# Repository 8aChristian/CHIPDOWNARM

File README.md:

# CHIPDOWNARM | Sub-GHz LoRaWAN & Industrial Telemetry Node

CHIPDOWNARM is a highly optimized, industrial-grade IoT telemetry edge node designed for mission-critical Sub-GHz LPWAN networks, remote monitoring, and smart agriculture deployments. Built around the high-performance **STMicroelectronics STM32WLE5** (ARM Cortex-M4 with integrated Sub-GHz LoRa/FSK transceiver), it delivers robust long-range communication with an ultra-low power footprint.

The board follows rigorous IPC (IPC-2152, IPC-2221) standards, featuring a wide-input high-efficiency switching power architecture (TPS62840), a highly stable 32MHz TCXO for RF precision, and an optimized 4-layer controlled-impedance stackup for impeccable RF Signal Integrity (SI) and Power Integrity (PI).

---

## 📸 Photorealistic 3D Renders

---

## 🏛️ System Architecture Diagram

```mermaid
flowchart TD
    subgraph PowerDomain["⚡ Power Architecture (1.8V - 6.5V)"]
        VIN["DC Power In (J1) / Li-SOCl2 / Li-Po"] --> F1["Polyfuse PTC (F1)"]
        F1 --> D1["TVS Diode Protection"]
        D1 --> U2["TI TPS62840 Buck (60nA Iq)"]
        U2 --> L1["1.5µH Shielded Inductor"]
        L1 --> VCC3["+3V0 System Rail"]
        VCC3 --> FB1["Ferrite Bead (FB1)"]
        FB1 --> VDDA["Filtered Analog Power (VDDA)"]
    end

    subgraph CoreDomain["🧠 Compute and RF Engine"]
        U1["STM32WLE5CCU6 (ARM Cortex-M4 @ 48MHz)"]
        Y1["32.000 MHz TCXO (Y1)"] -->|"RF Master Clock"| U1
        Y2["32.768 kHz RTC Crystal (Y2)"] -->|"Low Power RTC"| U1
        VCC3 --> U1
        VDDA --> U1
    end

    subgraph RFDomain["📡 Sub-GHz RF Frontend (150-960 MHz)"]
        U1 -->|"RF_PA_OUT"| RFFilt["LC Harmonics Filter & Matching Network"]
        RFFilt -->|"50Ω Coplanar Microstrip"| J2["SMA Edge-Mount Connector (J2)"]
    end

    subgraph SensorDomain["🌡️ Telemetry and Sensing"]
        U3["Sensirion SHTC3 (I2C)"] -->|"I2C1_SCL / I2C1_SDA"| U1
        VCC3 --> U3
    end

    subgraph DebugDomain["🔧 Diagnostics and Programming"]
        J3["Tag-Connect TC2030-IDC-NL"] -->|"SWDIO, SWCLK, NRST, SWO"| U1
    end

    classDef pwr fill:#f97316,stroke:#c2410c,stroke-width:2px,color:#fff;
    classDef core fill:#2563eb,stroke:#1d4ed8,stroke-width:2px,color:#fff;
    classDef rf fill:#16a34a,stroke:#15803d,stroke-width:2px,color:#fff;
    classDef sns fill:#9333ea,stroke:#7e22ce,stroke-width:2px,color:#fff;
    classDef dbg fill:#475569,stroke:#334155,stroke-width:2px,color:#fff;

    class PowerDomain,VIN,F1,D1,U2,L1,VCC3,FB1,VDDA pwr;
    class CoreDomain,U1,Y1,Y2 core;
    class RFDomain,RFFilt,J2 rf;
    class SensorDomain,U3 sns;
    class DebugDomain,J3 dbg;
```

---

## ⚡ Power Tree & Energy Profile

```mermaid
flowchart LR
    BATT["Battery / External Input<br/><b>1.8V - 6.5V</b>"] -->|F1: PTC Fuse| REG["TPS62840<br/><b>Buck Regulator</b><br/>Iq = 60 nA | Eff = 92%"]
    REG -->|VOUT = 3.0V| RAIL["+3V0 System Rail<br/>(Inner Layer 2 Plane)"]
    
    RAIL -->|"100nF + 4.7µF"| MCU["STM32WLE5 Core<br/>Sleep: 1.1 µA<br/>TX (+22dBm): 118 mA"]
    RAIL -->|"100nF"| SENS["SHTC3 Sensor<br/>Active: 800 µA<br/>Sleep: 0.2 µA"]
    RAIL -->|"100nF + TCXO Reg"| TCXO["32 MHz TCXO<br/>Warmup: 2 ms"]
    RAIL -->|FB1: Ferrite Filter| RF_ANA["RF & VDDA Power<br/>Multi-stage decoupling"]
```

---

## 🔬 PCB Layer Stackup & Controlled Impedance

The PCB is built on an industrial 4-Layer standard stackup (1.6mm nominal thickness, 1 oz / 35µm copper outer and inner layers) to guarantee excellent RF containment.

```text
========================================================================================
Layer 1 (Top / F.Cu): Component SMD Pads, 50Ω RF Coplanar Microstrips, Buck Power Loop
---------------------------------- Dielectric Prepreg (0.21mm, FR-4, Er=4.5) -----------
Layer 2 (Inner 1 / In1.Cu): Solid Continuous Ground Plane (GND) - Zero Slots
---------------------------------- Core Dielectric (1.065mm, FR-4, Er=4.5) -------------
Layer 3 (Inner 2 / In2.Cu): Dedicated +3V0 Power Plane & RF Return Shield
---------------------------------- Dielectric Prepreg (0.21mm, FR-4, Er=4.5) -----------
Layer 4 (Bottom / B.Cu): Digital Control Signals & Secondary Ground Shield
========================================================================================
```

### 🗺️ Individual Layer Vector Views

| Layer | Type | Function & High-Speed Details | Vector Preview |
| :--- | :--- | :--- | :--- |
| **L1 (F.Cu)** | Signal / RF | 50Ω Coplanar RF track, SMPS power loop, MCU breakouts | [View SVG](docs/img/layer_l1_top.svg) |
| **L2 (In1.Cu)** | Solid GND | 100% continuous reference ground, zero ground slots | [View SVG](docs/img/layer_l2_gnd.svg) |
| **L3 (In2.Cu)** | Power | Dedicated +3V0 power plane, ultra-low impedance distribution | [View SVG](docs/img/layer_l3_pwr.svg) |
| **L4 (B.Cu)** | Signal / Shield | I2C routing, debug traces, stitched ground plane | [View SVG](docs/img/layer_l4_bottom.svg) |

---

## ⚡ Technical Specifications

| Parameter | Specification | Engineering Details |
| :--- | :--- | :--- |
| **Input Supply Voltage** | **1.8V − 6.5V DC** | Polyfuse protection (F1) + Battery input conditioning for Li-Po/Li-SOCl2. |
| **Main Step-Down Converter** | **TI TPS62840 (1.8V-6.5V)** | Ultra-low $I_q$ (60 nA) high-efficiency buck regulator with compact shielded inductor. |
| **Main Processing Unit (MCU)** | **STM32WLE5CCU6** | ARM Cortex-M4 @ 48MHz, 256KB Flash, 64KB SRAM, integrated Sub-GHz Radio. |
| **Wireless Connectivity** | **LoRa / (G)FSK / (G)MSK** | Sub-GHz Radio (150 MHz to 960 MHz) compatible with LoRaWAN protocols. |
| **RF Clock Source** | **32.000 MHz TCXO** | High-stability Temperature Compensated Oscillator for precise RF modulation. |
| **Telemetry Sensor** | **Sensirion SHTC3** | Ultra-low power I2C Temperature and Humidity sensor (±2.0% RH, ±0.2°C). |
| **Debug Interface** | **SWD via Tag-Connect** | Zero-cost, zero-profile TC2030-IDC-NL footprint (No Legs) for SWD & SWO. |
| **RF Interface** | **SMA Edge-Mount** | 50Ω impedance-matched Coplanar Waveguide routing to SMA connector. |
| **Design Rule Check (DRC)** | **100% Passed (0 Errors)** | 0 Unrouted airwires, 0 clearance errors, full IPC-2221 compliance. |

---

## 📋 Comprehensive Bill of Materials (BOM)

| Item | Qty | Component / Value | Manufacturer | MPN | Description |
| :--- | :--- | :--- | :--- | :--- | :--- |
| **U1** | 1 | **STM32WLE5CCU6** | STMicroelectronics | STM32WLE5CCU6 | ARM Cortex-M4 Sub-GHz LoRa SoC (UFQFPN-48) |
| **U2** | 1 | **TPS62840DLCR** | Texas Instruments | TPS62840DLCR | Ultra-Low Iq Step-Down Converter |
| **U3** | 1 | **SHTC3** | Sensirion | SHTC3 | I2C Humidity and Temperature Sensor |
| **Y1** | 1 | **NT2016SA-32M** | NDK | NT2016SA-32M | 32.000MHz TCXO (Temperature Compensated) |
| **J1** | 1 | **SMA Edge-Mount** | Amphenol | 132136 | 50Ω SMA RF Connector |
| **J3** | 1 | **TC2030-IDC-NL** | Tag-Connect | TC2030-IDC-NL | 6-pin No-Legs SWD Programming Header |

*(For passive components, resistors, MLCCs, and exact footprints, please see [CHIPDOWNARM_BOM.xml](CHIPDOWNARM_BOM.xml))*

---

## 📁 Repository Structure

```text
CHIPDOWNARM/
├── CHIPDOWNARM.kicad_pcb        # KiCad 8/9 PCB Layout File (4-Layer, 0 DRC Errors)
├── CHIPDOWNARM.kicad_sch        # KiCad Schematic File
├── CHIPDOWNARM.kicad_pro        # KiCad Project Definitions
├── CHIPDOWNARM_Schematic.pdf    # Complete vector schematic PDF
├── CHIPDOWNARM.step             # High-precision 3D mechanical model (STEP AP214)
├── CHIPDOWNARM_BOM.xml          # Sourcing Bill of Materials
├── gerbers/                     # Standard RS-274X Fabrication Gerbers & Excellon Drills
│   ├── CHIPDOWNARM-F_Cu.gtl     # Top Copper Layer
│   ├── CHIPDOWNARM-In1_Cu.g1    # Layer 2 Ground Plane
│   ├── CHIPDOWNARM-In2_Cu.g2    # Layer 3 Power Plane
│   ├── CHIPDOWNARM-B_Cu.gbl     # Bottom Copper Layer
│   ├── CHIPDOWNARM.drl          # NC Drill file
│   └── ...                      # Masks, silkscreens, edge cuts
├── docs/
│   └── img/                     # 3D Photorealistic raytracing renders & SVG layer previews
│       ├── render_isometric_top.png
│       ├── render_isometric_bottom.png
│       ├── render_top.png
│       └── layer_l*.svg
├── .gitignore                   # Clean Git configuration for EDA projects
└── README.md                    # Comprehensive hardware documentation
```

---

## 🚀 How to Build & Open the Project

### Prerequisites
* EDA Suite: **[KiCad 8.0+](https://www.kicad.org/)** (Fully tested on KiCad 8 & 9).

### Opening in KiCad
1. Clone the repository:
   ```bash
   git clone https://github.com/8aChristian/CHIPDOWNARM.git
   cd CHIPDOWNARM
   ```
2. Open `CHIPDOWNARM.kicad_pro` inside KiCad.
3. Open the **Schematic Editor** to review the architecture.
4. Open the **PCB Editor** and hit `B` to recalculate all zone fills and inspect the perfectly clean 4-layer layout.
5. Press `Alt + 3` to open the interactive 3D viewer.

---

## 📜 License & Author

**Author**: Christian Ochoa ([@8aChristian](https://github.com/8aChristian))  
**Status**: Ready for Fabrication (0 Unrouted, 0 DRC Violations)  
**License**: Released under the MIT License.

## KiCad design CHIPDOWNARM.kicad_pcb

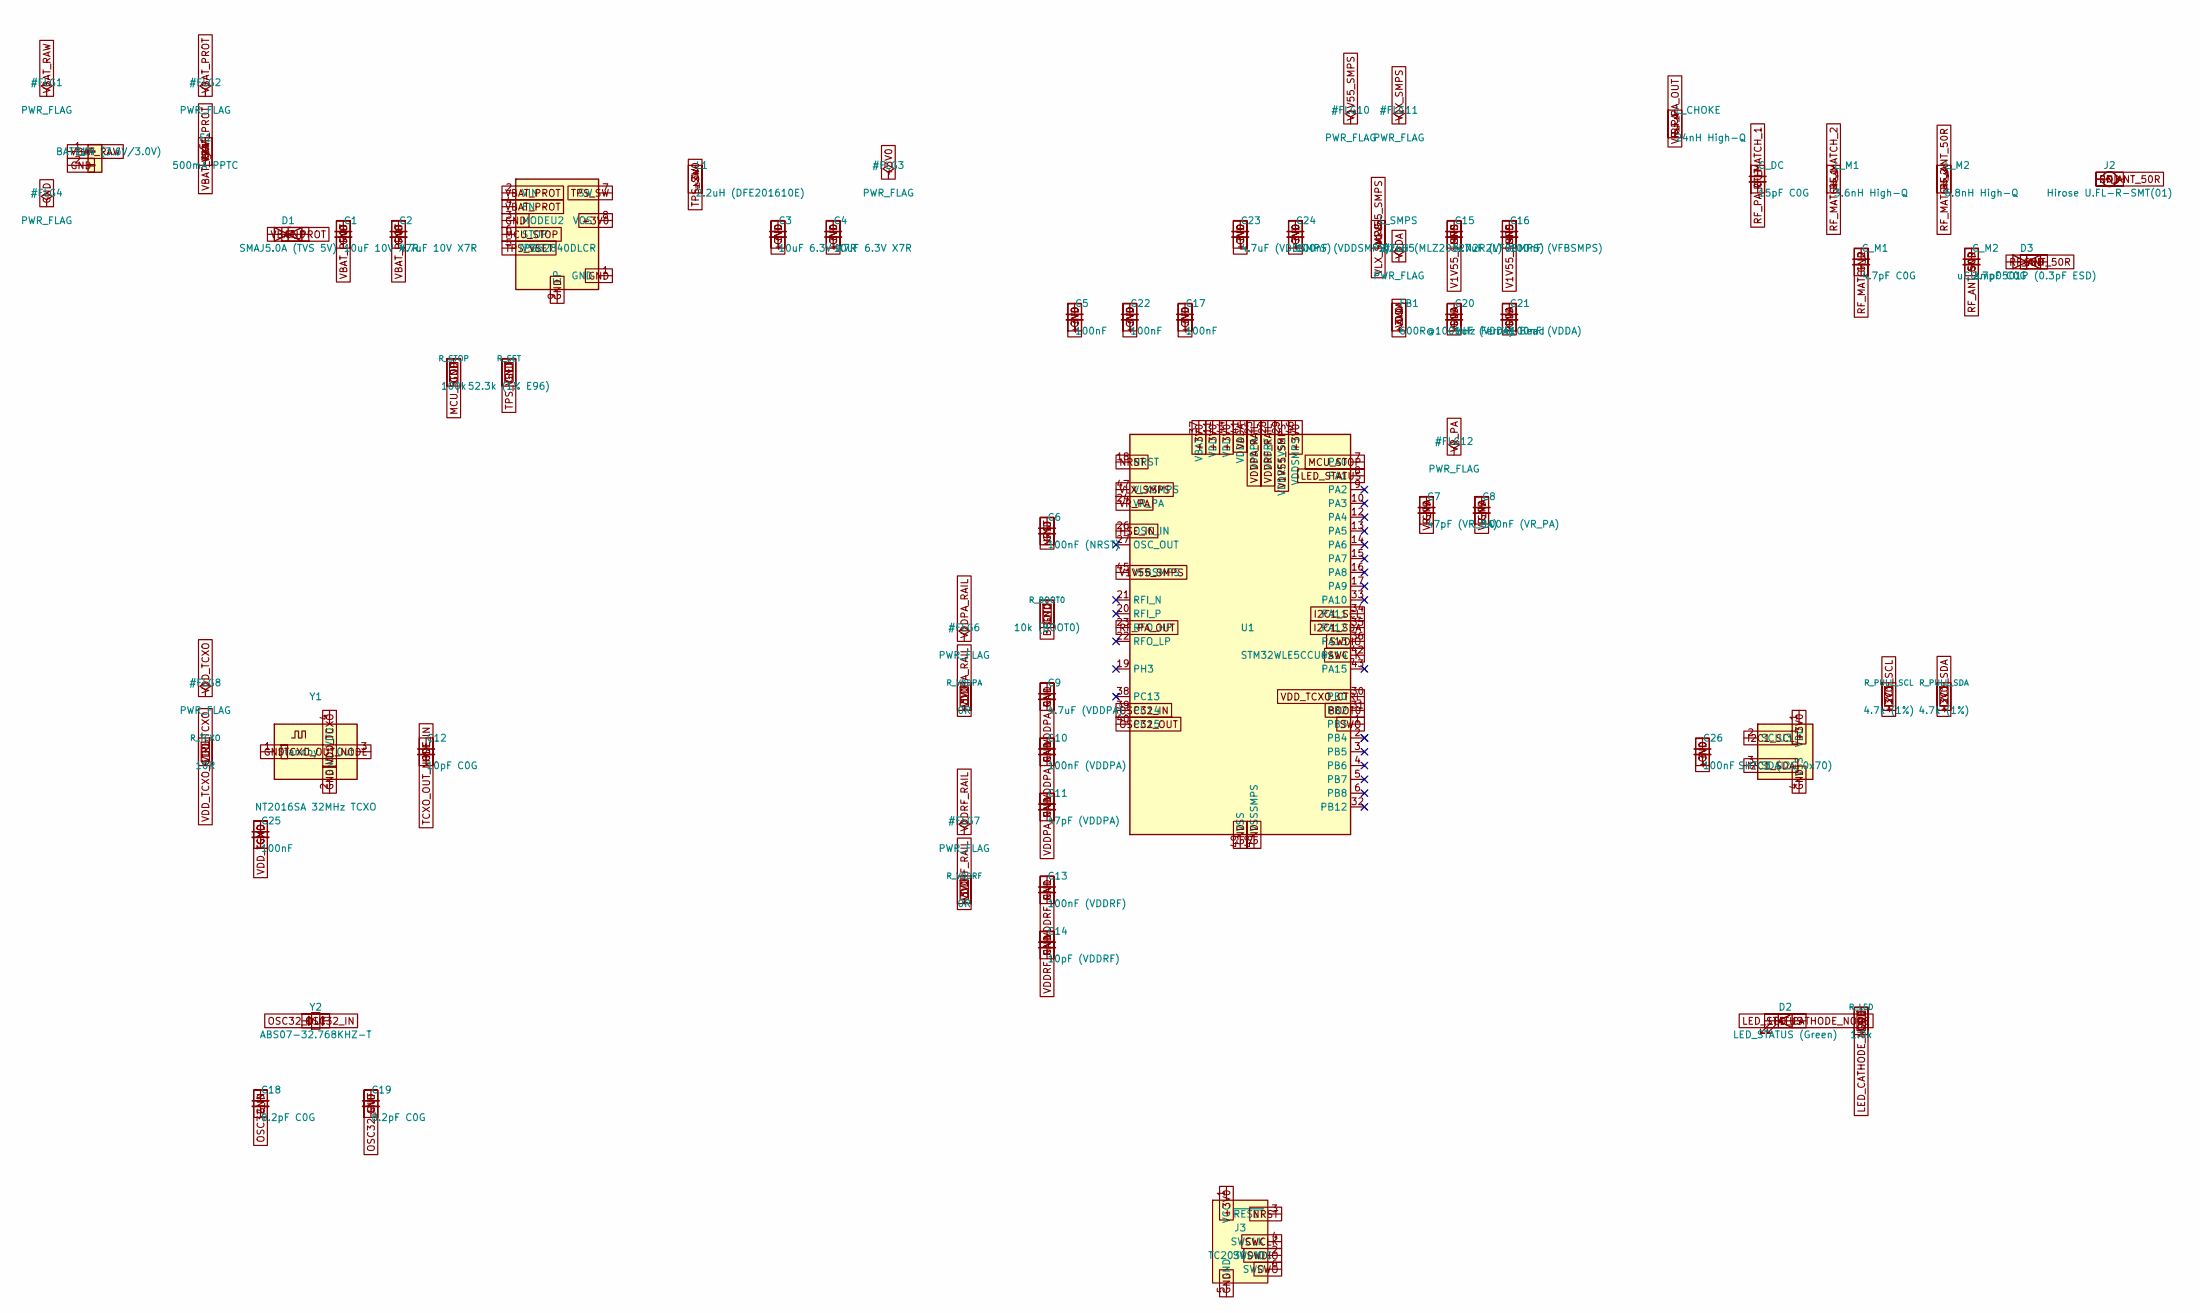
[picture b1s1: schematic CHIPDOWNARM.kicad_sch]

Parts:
C1: 10uF 10V X7R; C_0603_1608Metric
C2: 4.7uF 10V X7R; C_0603_1608Metric
C3, C4: 10uF 6.3V X7R; C_0603_1608Metric
C5, C17, C22, C25, C26: 100nF; C_0402_1005Metric
C6: 100nF (NRST); C_0402_1005Metric
C7: 47pF (VR_PA); C_0402_1005Metric
C8: 100nF (VR_PA); C_0402_1005Metric
C9: 4.7uF (VDDPA); C_0603_1608Metric
C10: 100nF (VDDPA); C_0402_1005Metric
C11: 47pF (VDDPA); C_0402_1005Metric
C12: 10pF C0G; C_0402_1005Metric
C13: 100nF (VDDRF); C_0402_1005Metric
C14: 10pF (VDDRF); C_0402_1005Metric
C15: 4.7uF (VFBSMPS); C_0603_1608Metric
C16: 100nF (VFBSMPS); C_0402_1005Metric
C18, C19: 8.2pF C0G; C_0402_1005Metric
C20: 1uF (VDDA); C_0402_1005Metric
C21: 100nF (VDDA); C_0402_1005Metric
C23: 4.7uF (VDDSMPS); C_0603_1608Metric
C24: 100nF (VDDSMPS); C_0402_1005Metric
C_DC: 15pF C0G; C_0402_1005Metric
C_M1: 4.7pF C0G; C_0402_1005Metric
C_M2: 2.7pF C0G; C_0402_1005Metric
D1: SMAJ5.0A (TVS 5V); D_0603_1608Metric
D2: LED_STATUS (Green); LED_0603_1608Metric
D3: uClamp0501P (0.3pF ESD); D_0402_1005Metric
F1: 500mA PPTC; Fuse_0805_2012Metric
FB1: 600R@100MHz Ferrite Bead; L_0402_1005Metric
J1: BATT_IN (3.6V/3.0V); PinHeader_1x02_P2.54mm_Vertical
J2: Hirose U.FL-R-SMT(01); U.FL_Hirose_U.FL-R-SMT-1_Vertical
J3: TC2030-IDC; Tag-Connect_TC2030-IDC-FP_2x03_P1.27mm_Vertical
L1: 2.2uH (DFE201610E); L_0805_2012Metric
L_CHOKE: 24nH High-Q; L_0402_1005Metric
L_M1: 3.6nH High-Q; L_0402_1005Metric
L_M2: 6.8nH High-Q; L_0402_1005Metric
L_SMPS: 2.2uH (MLZ2012N2R2L); L_0805_2012Metric
R_BOOT0: 10k (BOOT0); R_0402_1005Metric
R_LED: 1.0k; R_0402_1005Metric
R_PULL_SCL: 4.7k (1%); R_0402_1005Metric
R_PULL_SDA: 4.7k (1%); R_0402_1005Metric
R_SET: 52.3k (1% E96); R_0402_1005Metric
R_STOP: 100k; R_0402_1005Metric
R_TCXO: 10R; R_0402_1005Metric
R_VDDPA: 0R; R_0402_1005Metric
R_VDDRF: 0R; R_0402_1005Metric
U1: STM32WLE5CCU6; QFN-48-1EP_7x7mm_P0.5mm_EP5.6x5.6mm
U2: TPS62840DLCR; Texas_VSON-HR-8_1.5x2mm_P0.5mm
U3: SHTC3 (I2C 0x70); Sensirion_DFN-4-1EP_2x2mm_P1mm_EP0.7x1.6mm
Y1: NT2016SA 32MHz TCXO; Oscillator_SMD_SiT_PQFN-4Pin_2.0x1.6mm
Y2: ABS07-32.768KHZ-T; Crystal_SMD_3215-2Pin_3.2x1.5mm

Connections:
+3V0: C3.1, C4.1, C5.1, C17.1, C22.1, C23.1, C24.1, C26.1, FB1.1, J3.1 (VCC), L1.2, R_PULL_SCL.1, R_PULL_SDA.1, R_VDDPA.1, R_VDDRF.1, U1.11 (VDD), U1.37 (VBAT), U1.44 (VDD), U1.46 (VDDSMPS), U2.8 (VOS), U3.1 (VDD)
BOOT0: R_BOOT0.1, U1.31 (PB2)
GND: C1.2, C2.2, C3.2, C4.2, C5.2, C6.2, C7.2, C8.2, C9.2, C10.2, C11.2, C13.2, C14.2, C15.2, C16.2, C17.2, C18.2, C19.2, C20.2, C21.2, C22.2, C23.2, C24.2, C25.2, C26.2, C_M1.2, C_M2.2, D1.2 (A2), D3.2 (A2), J1.2, J2.2 (Ext), J3.5 (GND), R_BOOT0.2, R_LED.2, R_SET.2, R_STOP.2, U1.48 (VSSSMPS), U1.49 (VSS), U2.1 (GND), U2.3 (MODE), U2.9 (EP), U3.4 (VSS), Y1.1 (Standby), Y1.2 (GND)
HSE_IN: C12.2, U1.26 (OSC_IN)
I2C1_SCL: R_PULL_SCL.2, U1.34 (PA11), U3.2 (SCL)
I2C1_SDA: R_PULL_SDA.2, U1.35 (PA12), U3.3 (SDA)
LED_CATHODE_NODE: D2.1 (K), R_LED.1
LED_STATUS: D2.2 (A), U1.8 (PA1)
MCU_STOP: R_STOP.1, U1.7 (PA0), U2.6 (STOP)
NRST: C6.1, J3.3 (~RESET), U1.18 (NRST)
OSC32_IN: C18.1, U1.39 (PC14), Y2.1
OSC32_OUT: C19.1, U1.40 (PC15), Y2.2
RF_ANT_50R: C_M2.1, D3.1 (A1), J2.1 (In), L_M2.2
RF_MATCH_1: C_DC.2, L_M1.1
RF_MATCH_2: C_M1.1, L_M1.2, L_M2.1
RF_PA_OUT: C_DC.1, L_CHOKE.2, U1.23 (RFO_HP)
SWCLK: J3.4 (SWCLK), U1.42 (PA14)
SWDIO: J3.2 (SWDIO), U1.36 (PA13)
SWO: J3.6 (SWO), U1.1 (PB3)
TCXO_OUT_NODE: C12.1, Y1.3 (Out)
TPS_SW: L1.1, U2.7 (SW)
TPS_VSET: R_SET.1, U2.5 (VSET)
V1V55_SMPS: C15.1, C16.1, L_SMPS.2, U1.29 (VDDRF1V55), U1.45 (VFBSMPS)
VBAT_PROT: C1.1, C2.1, D1.1 (A1), F1.2, U2.2 (VIN), U2.4 (EN)
VBAT_RAW: F1.1, J1.1
VDDA: C20.1, C21.1, FB1.2, U1.41 (VDDA)
VDDPA_RAIL: C9.1, C10.1, C11.1, R_VDDPA.2, U1.25 (VDDPA)
VDDRF_RAIL: C13.1, C14.1, R_VDDRF.2, U1.28 (VDDRF)
VDD_TCXO: C25.1, R_TCXO.2, Y1.4 (VDD)
VDD_TCXO_CTRL: R_TCXO.1, U1.30 (PB0)
VLX_SMPS: L_SMPS.1, U1.47 (VLXSMPS)
VR_PA: C7.1, C8.1, L_CHOKE.1, U1.24 (VR_PA)

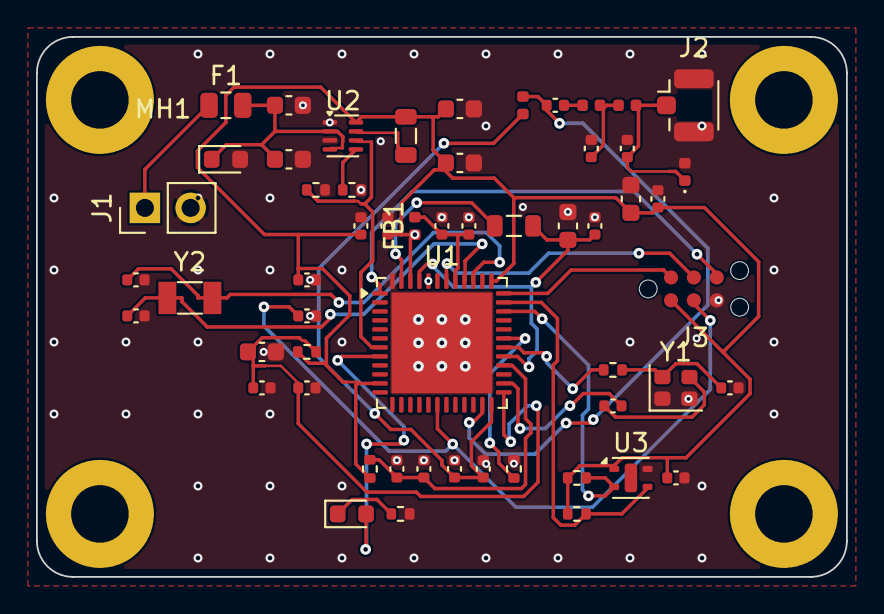
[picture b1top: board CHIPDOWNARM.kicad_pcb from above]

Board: 4 copper layers, 45.0 x 30.0 mm, 60 parts (0 on the bottom side), 32 nets.

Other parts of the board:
MH1, MH2, MH3, MH4: MountingHole_3.2mm_M3_Pad_Via
